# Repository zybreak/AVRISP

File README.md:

AVR ISP Shield for Arduino
===========================

This is an AVR ISP Shield for Arduino

Repository Contents
-------------------
* **/Hardware** - Kicad PCB .pro .sch and .brb files and PDF of Schematic
* **/Software** - Arduino Sketch for Using the Board

Version History
---------------
* V0.1 Functions well for the ATTiny85 but seem to be having problems with the ATMega328 - working on it!
* V1.0 Fully working - has a rearrange from previous versions which avoids grounding on the USB connector on an Uno.
* V1.3 Board update
   - Updated the LED pins to match the ones used in the arduino as isp sketch.
   - Added reset capacitor to prevent the arduino from resetting before programming.
   - Added support for an external clock.

License Information
-------------------
The hardware is released under [Creative Commons Share-alike 3.0](http://creativecommons.org/licenses/by-sa/3.0/).  
All other code is open source so please feel free to do anything you want with it; you buy me a beer if you use this and we meet someday ([Beerware license](http://en.wikipedia.org/wiki/Beerware)).
Also this boiler plate is yoinked from Sparkfun with thanks.

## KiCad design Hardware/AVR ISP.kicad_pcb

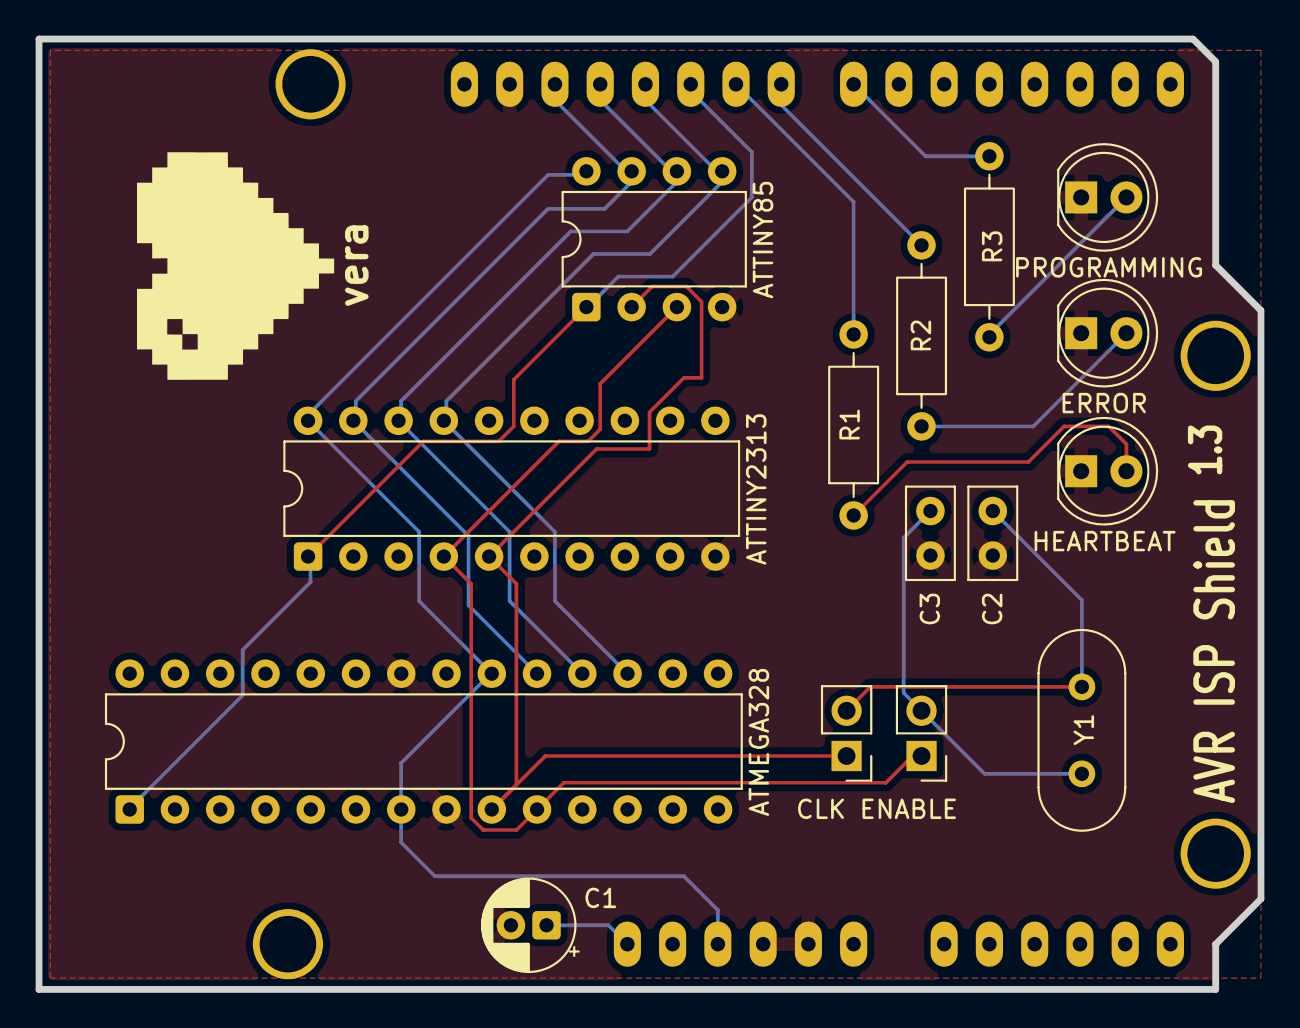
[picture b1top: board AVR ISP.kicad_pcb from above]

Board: 2 copper layers, 68.6 x 53.3 mm, 16 parts (0 on the bottom side), 17 nets.

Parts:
C1: C_Polarized; CP_Radial_D5.0mm_P2.00mm
C2, C3: C_Small; C_Disc_D5.0mm_W2.5mm_P2.50mm
CLK ENABLE: PinHeader_1x02_P2.54mm_Vertical
D1: HEARTBEAT; LED_D5.0mm
D2: ERROR; LED_D5.0mm
D3: PROGRAMMING; LED_D5.0mm
IC1: ATMEGA328; DIP-28_W7.62mm
IC2: ATTINY2313; DIP-20_W7.62mm
IC3: ATTINY85; DIP-8_W7.62mm
JP2: PinHeader_1x02_P2.54mm_Vertical
R1, R2, R3: 330; R_Axial_DIN0207_L6.3mm_D2.5mm_P10.16mm_Horizontal
SHIELD1: ARDUINO_SHIELD
Y1: Crystal; Crystal_HC49-4H_Vertical

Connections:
+5V: IC1.7 (VCC), IC1.20 (AVCC), IC2.20 (VCC), IC3.8 (VCC), SHIELD1.5V
GND: C1.2, C2.2, C3.2, D1.1 (K), D2.1 (K), D3.1 (K), IC1.8 (GND), IC1.22 (GND), IC2.10 (GND), IC3.4 (GND), SHIELD1.GND1, SHIELD1.GND2, SHIELD1.GND3
unnamed: C1.1, SHIELD1.RST
unnamed: D1.2 (A), R1.1
unnamed: D2.2 (A), R2.1
unnamed: D3.2 (A), R3.1
unnamed: IC1.17 (PB3), IC2.17 (PB5), IC3.5 (AREF/PB0), SHIELD1.11
unnamed: IC1.18 (PB4), IC2.18 (PB6), IC3.6 (PB1), SHIELD1.12
unnamed: IC1.19 (PB5), IC2.19 (PB7), IC3.7 (PB2), SHIELD1.13
unnamed: CLK ENABLE.1 (A), IC1.9 (XTAL1/PB6), IC2.5 (PA0/XTAL1), IC3.2 (XTAL1/PB3)
unnamed: IC1.10 (XTAL2/PB7), IC2.4 (PA1/XTAL2), IC3.3 (XTAL2/PB4), JP2.1 (A)
unnamed: IC1.1 (~RESET/PC6), IC2.1 (PA2/~RESET), IC3.1 (~RESET/PB5), SHIELD1.10
unnamed: C2.1, CLK ENABLE.2 (B), Y1.2
unnamed: C3.1, JP2.2 (B), Y1.1
unnamed: R1.2, SHIELD1.9
unnamed: R2.2, SHIELD1.8
unnamed: R3.2, SHIELD1.7

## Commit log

2026-03-28 KiCad 10, reset cap, correct LED, opt ext clk
    Updated to KiCad 10 project files
    Added a capacitor between arduino reset and ground preventing a reset
    before programming.
    Updated LED pins
    Added support for an external clock source
2026-03-28 Updated 3d render and schematic pdf
2026-03-28 removed generated files, source of truth is in kicad files
2026-04-15 Updated PCB and images
    Updated PCB removing plating around the four sheild holes
    Added an image of the built PCB
